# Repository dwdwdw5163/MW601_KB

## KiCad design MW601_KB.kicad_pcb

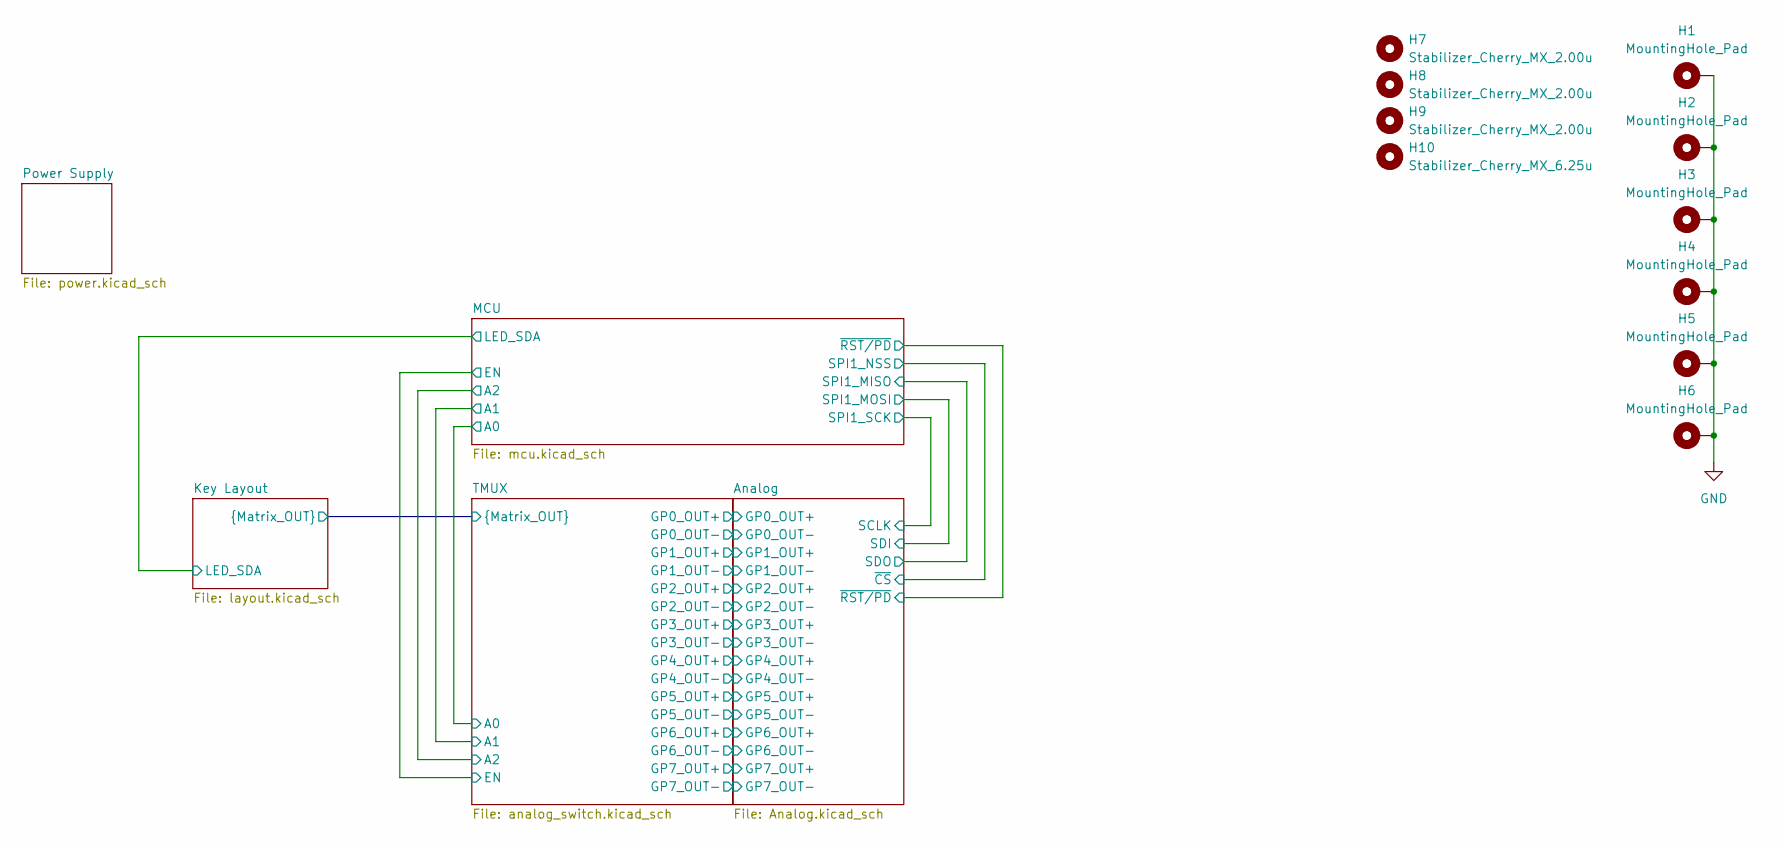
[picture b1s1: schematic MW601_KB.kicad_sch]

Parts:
H1: MountingHole_Pad; PKRHC
H2, H3, H6: MountingHole_Pad; PKRH
H4, H5: MountingHole_Pad; PKRHSL
H7, H8, H9: Stabilizer_Cherry_MX_2.00u
H10: Stabilizer_Cherry_MX_6.25u

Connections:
GND: H1.1, H2.1, H3.1, H4.1, H5.1, H6.1; also elsewhere on the board

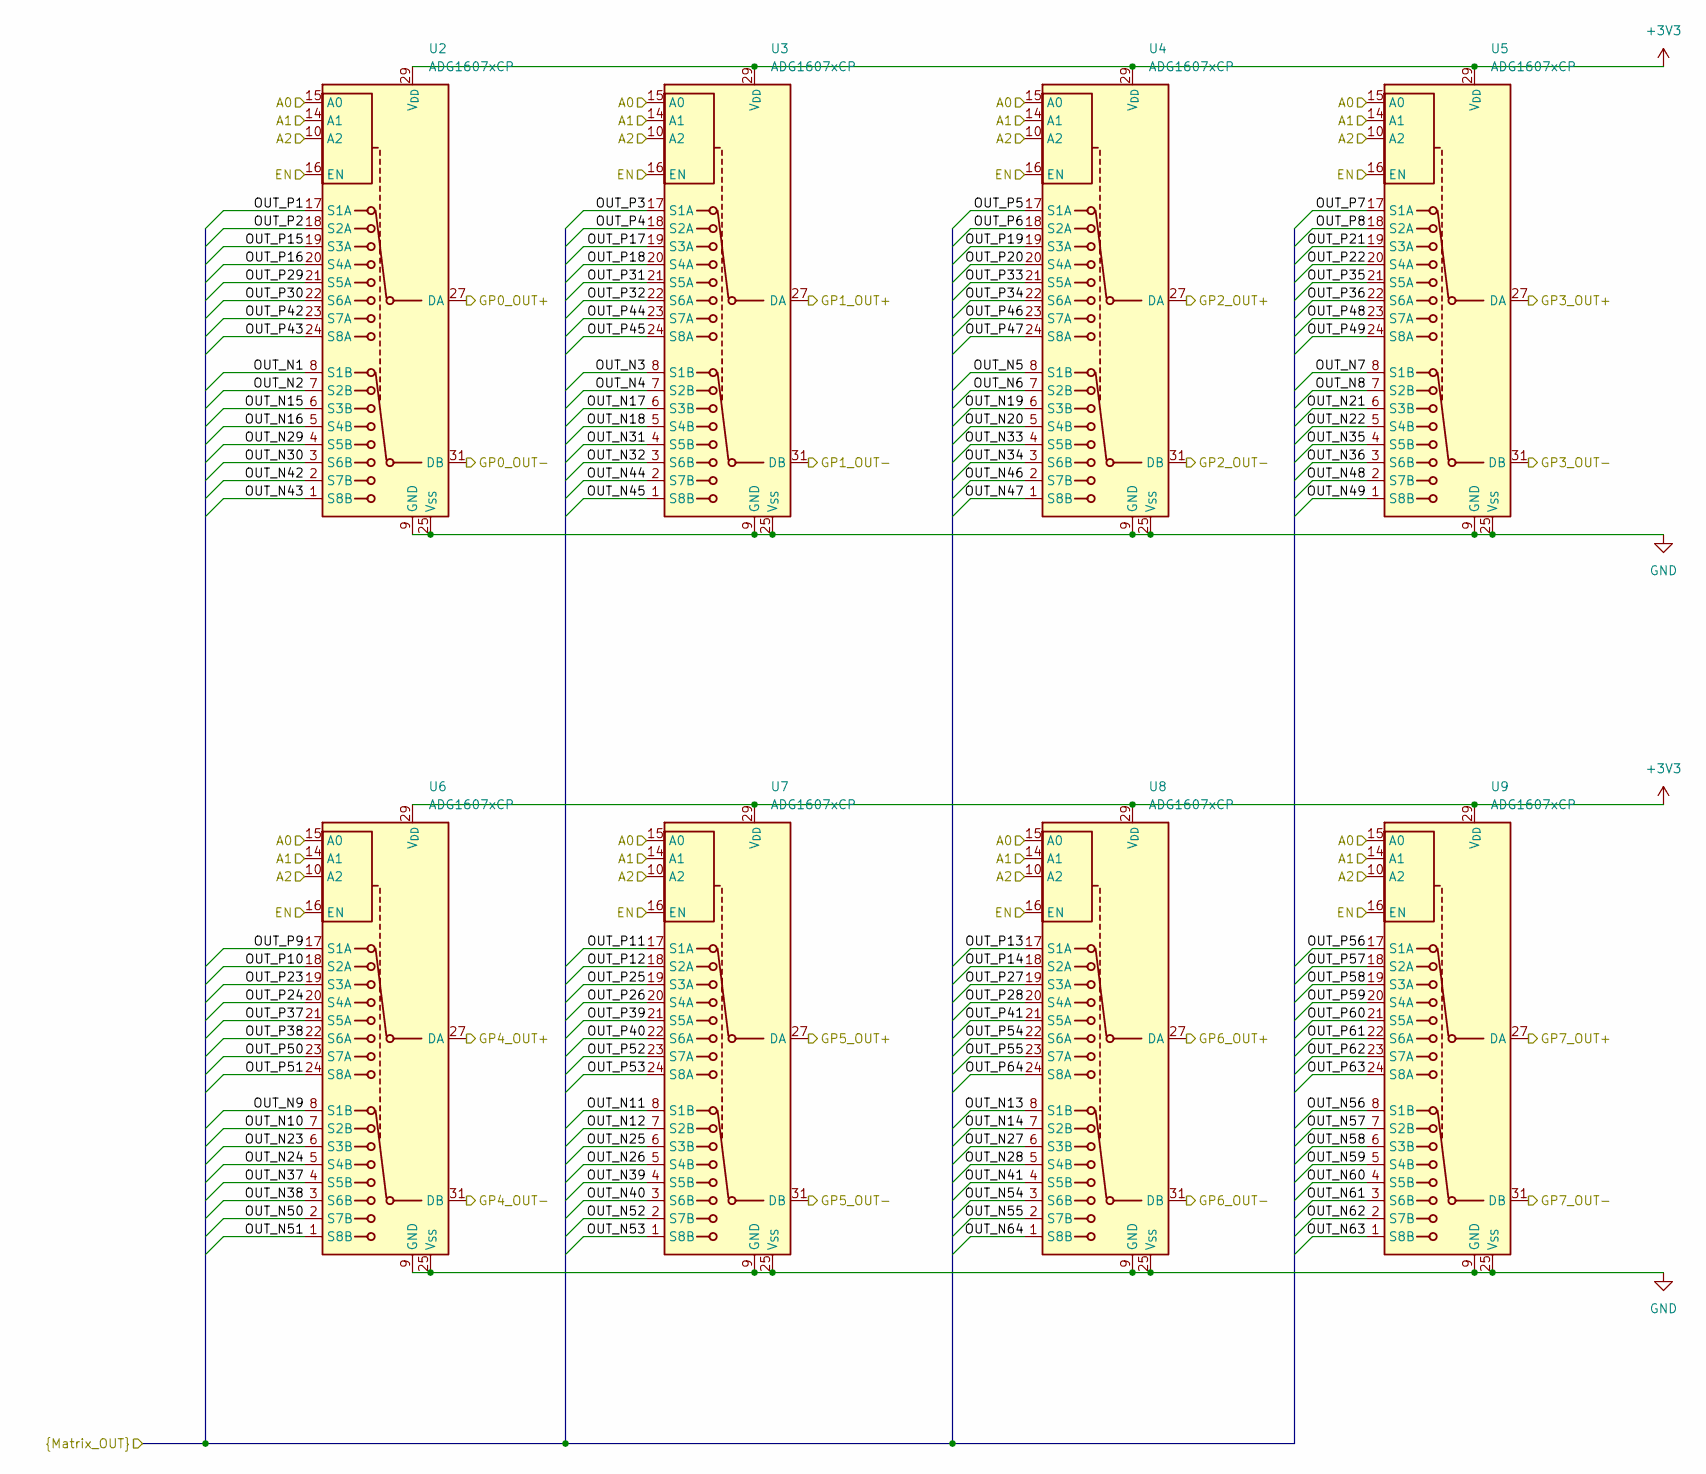
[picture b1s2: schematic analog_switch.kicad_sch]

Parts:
U2, U3, U4, U5, U6, U7, U8, U9: ADG1607xCP; LFCSP-32-1EP_5x5mm_P0.5mm_EP3.1x3.1mm

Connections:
+3V3: U2.29 (V_{DD}), U3.29 (V_{DD}), U4.29 (V_{DD}), U5.29 (V_{DD}), U6.29 (V_{DD}), U7.29 (V_{DD}), U8.29 (V_{DD}), U9.29 (V_{DD}); also elsewhere on the board
/Analog/GP0_OUT+: U2.27 (DA); also elsewhere on the board
/Analog/GP0_OUT-: U2.31 (DB); also elsewhere on the board
/Analog/GP1_OUT+: U3.27 (DA); also elsewhere on the board
/Analog/GP1_OUT-: U3.31 (DB); also elsewhere on the board
/Analog/GP2_OUT+: U4.27 (DA); also elsewhere on the board
/Analog/GP2_OUT-: U4.31 (DB); also elsewhere on the board
/Analog/GP3_OUT+: U5.27 (DA); also elsewhere on the board
/Analog/GP3_OUT-: U5.31 (DB); also elsewhere on the board
/Analog/GP4_OUT+: U6.27 (DA); also elsewhere on the board
/Analog/GP4_OUT-: U6.31 (DB); also elsewhere on the board
/Analog/GP5_OUT+: U7.27 (DA); also elsewhere on the board
/Analog/GP5_OUT-: U7.31 (DB); also elsewhere on the board
/Analog/GP6_OUT+: U8.27 (DA); also elsewhere on the board
/Analog/GP6_OUT-: U8.31 (DB); also elsewhere on the board
/Analog/GP7_OUT+: U9.27 (DA); also elsewhere on the board
/Analog/GP7_OUT-: U9.31 (DB); also elsewhere on the board
/Key Layout/OUT_N1: U2.8 (S1B); also elsewhere on the board
/Key Layout/OUT_N2: U2.7 (S2B); also elsewhere on the board
/Key Layout/OUT_N3: U3.8 (S1B); also elsewhere on the board
/Key Layout/OUT_N4: U3.7 (S2B); also elsewhere on the board
/Key Layout/OUT_N5: U4.8 (S1B); also elsewhere on the board
/Key Layout/OUT_N6: U4.7 (S2B); also elsewhere on the board
/Key Layout/OUT_N7: U5.8 (S1B); also elsewhere on the board
/Key Layout/OUT_N8: U5.7 (S2B); also elsewhere on the board
/Key Layout/OUT_N9: U6.8 (S1B); also elsewhere on the board
/Key Layout/OUT_N10: U6.7 (S2B); also elsewhere on the board
/Key Layout/OUT_N11: U7.8 (S1B); also elsewhere on the board
/Key Layout/OUT_N12: U7.7 (S2B); also elsewhere on the board
/Key Layout/OUT_N13: U8.8 (S1B); also elsewhere on the board
/Key Layout/OUT_N14: U8.7 (S2B); also elsewhere on the board
/Key Layout/OUT_N15: U2.6 (S3B); also elsewhere on the board
/Key Layout/OUT_N16: U2.5 (S4B); also elsewhere on the board
/Key Layout/OUT_N17: U3.6 (S3B); also elsewhere on the board
/Key Layout/OUT_N18: U3.5 (S4B); also elsewhere on the board
/Key Layout/OUT_N19: U4.6 (S3B); also elsewhere on the board
/Key Layout/OUT_N20: U4.5 (S4B); also elsewhere on the board
/Key Layout/OUT_N21: U5.6 (S3B); also elsewhere on the board
/Key Layout/OUT_N22: U5.5 (S4B); also elsewhere on the board
/Key Layout/OUT_N23: U6.6 (S3B); also elsewhere on the board
/Key Layout/OUT_N24: U6.5 (S4B); also elsewhere on the board
/Key Layout/OUT_N25: U7.6 (S3B); also elsewhere on the board
/Key Layout/OUT_N26: U7.5 (S4B); also elsewhere on the board
/Key Layout/OUT_N27: U8.6 (S3B); also elsewhere on the board
/Key Layout/OUT_N28: U8.5 (S4B); also elsewhere on the board
/Key Layout/OUT_N29: U2.4 (S5B); also elsewhere on the board
/Key Layout/OUT_N30: U2.3 (S6B); also elsewhere on the board
/Key Layout/OUT_N31: U3.4 (S5B); also elsewhere on the board
/Key Layout/OUT_N32: U3.3 (S6B); also elsewhere on the board
/Key Layout/OUT_N33: U4.4 (S5B); also elsewhere on the board
/Key Layout/OUT_N34: U4.3 (S6B); also elsewhere on the board
/Key Layout/OUT_N35: U5.4 (S5B); also elsewhere on the board
/Key Layout/OUT_N36: U5.3 (S6B); also elsewhere on the board
/Key Layout/OUT_N37: U6.4 (S5B); also elsewhere on the board
/Key Layout/OUT_N38: U6.3 (S6B); also elsewhere on the board
/Key Layout/OUT_N39: U7.4 (S5B); also elsewhere on the board
/Key Layout/OUT_N40: U7.3 (S6B); also elsewhere on the board
/Key Layout/OUT_N41: U8.4 (S5B); also elsewhere on the board
/Key Layout/OUT_N42: U2.2 (S7B); also elsewhere on the board
/Key Layout/OUT_N43: U2.1 (S8B); also elsewhere on the board
/Key Layout/OUT_N44: U3.2 (S7B); also elsewhere on the board
/Key Layout/OUT_N45: U3.1 (S8B); also elsewhere on the board
/Key Layout/OUT_N46: U4.2 (S7B); also elsewhere on the board
/Key Layout/OUT_N47: U4.1 (S8B); also elsewhere on the board
/Key Layout/OUT_N48: U5.2 (S7B); also elsewhere on the board
/Key Layout/OUT_N49: U5.1 (S8B); also elsewhere on the board
/Key Layout/OUT_N50: U6.2 (S7B); also elsewhere on the board
/Key Layout/OUT_N51: U6.1 (S8B); also elsewhere on the board
/Key Layout/OUT_N52: U7.2 (S7B); also elsewhere on the board
/Key Layout/OUT_N53: U7.1 (S8B); also elsewhere on the board
/Key Layout/OUT_N54: U8.3 (S6B); also elsewhere on the board
/Key Layout/OUT_N55: U8.2 (S7B); also elsewhere on the board
/Key Layout/OUT_N56: U9.8 (S1B); also elsewhere on the board
/Key Layout/OUT_N57: U9.7 (S2B); also elsewhere on the board
/Key Layout/OUT_N58: U9.6 (S3B); also elsewhere on the board
/Key Layout/OUT_N59: U9.5 (S4B); also elsewhere on the board
/Key Layout/OUT_N60: U9.4 (S5B); also elsewhere on the board
/Key Layout/OUT_N61: U9.3 (S6B); also elsewhere on the board
/Key Layout/OUT_N62: U9.2 (S7B); also elsewhere on the board
/Key Layout/OUT_N63: U9.1 (S8B); also elsewhere on the board
/Key Layout/OUT_N64: U8.1 (S8B); also elsewhere on the board
/Key Layout/OUT_P1: U2.17 (S1A); also elsewhere on the board
/Key Layout/OUT_P2: U2.18 (S2A); also elsewhere on the board
/Key Layout/OUT_P3: U3.17 (S1A); also elsewhere on the board
/Key Layout/OUT_P4: U3.18 (S2A); also elsewhere on the board
/Key Layout/OUT_P5: U4.17 (S1A); also elsewhere on the board
/Key Layout/OUT_P6: U4.18 (S2A); also elsewhere on the board
/Key Layout/OUT_P7: U5.17 (S1A); also elsewhere on the board
/Key Layout/OUT_P8: U5.18 (S2A); also elsewhere on the board
/Key Layout/OUT_P9: U6.17 (S1A); also elsewhere on the board
/Key Layout/OUT_P10: U6.18 (S2A); also elsewhere on the board
/Key Layout/OUT_P11: U7.17 (S1A); also elsewhere on the board
/Key Layout/OUT_P12: U7.18 (S2A); also elsewhere on the board
/Key Layout/OUT_P13: U8.17 (S1A); also elsewhere on the board
/Key Layout/OUT_P14: U8.18 (S2A); also elsewhere on the board
/Key Layout/OUT_P15: U2.19 (S3A); also elsewhere on the board
/Key Layout/OUT_P16: U2.20 (S4A); also elsewhere on the board
/Key Layout/OUT_P17: U3.19 (S3A); also elsewhere on the board
/Key Layout/OUT_P18: U3.20 (S4A); also elsewhere on the board
/Key Layout/OUT_P19: U4.19 (S3A); also elsewhere on the board
/Key Layout/OUT_P20: U4.20 (S4A); also elsewhere on the board
/Key Layout/OUT_P21: U5.19 (S3A); also elsewhere on the board
/Key Layout/OUT_P22: U5.20 (S4A); also elsewhere on the board
/Key Layout/OUT_P23: U6.19 (S3A); also elsewhere on the board
/Key Layout/OUT_P24: U6.20 (S4A); also elsewhere on the board
/Key Layout/OUT_P25: U7.19 (S3A); also elsewhere on the board
/Key Layout/OUT_P26: U7.20 (S4A); also elsewhere on the board
/Key Layout/OUT_P27: U8.19 (S3A); also elsewhere on the board
/Key Layout/OUT_P28: U8.20 (S4A); also elsewhere on the board
/Key Layout/OUT_P29: U2.21 (S5A); also elsewhere on the board
/Key Layout/OUT_P30: U2.22 (S6A); also elsewhere on the board
/Key Layout/OUT_P31: U3.21 (S5A); also elsewhere on the board
/Key Layout/OUT_P32: U3.22 (S6A); also elsewhere on the board
/Key Layout/OUT_P33: U4.21 (S5A); also elsewhere on the board
/Key Layout/OUT_P34: U4.22 (S6A); also elsewhere on the board
/Key Layout/OUT_P35: U5.21 (S5A); also elsewhere on the board
/Key Layout/OUT_P36: U5.22 (S6A); also elsewhere on the board
/Key Layout/OUT_P37: U6.21 (S5A); also elsewhere on the board
/Key Layout/OUT_P38: U6.22 (S6A); also elsewhere on the board
/Key Layout/OUT_P39: U7.21 (S5A); also elsewhere on the board
/Key Layout/OUT_P40: U7.22 (S6A); also elsewhere on the board
/Key Layout/OUT_P41: U8.21 (S5A); also elsewhere on the board
/Key Layout/OUT_P42: U2.23 (S7A); also elsewhere on the board
/Key Layout/OUT_P43: U2.24 (S8A); also elsewhere on the board
/Key Layout/OUT_P44: U3.23 (S7A); also elsewhere on the board
/Key Layout/OUT_P45: U3.24 (S8A); also elsewhere on the board
/Key Layout/OUT_P46: U4.23 (S7A); also elsewhere on the board
/Key Layout/OUT_P47: U4.24 (S8A); also elsewhere on the board
/Key Layout/OUT_P48: U5.23 (S7A); also elsewhere on the board
/Key Layout/OUT_P49: U5.24 (S8A); also elsewhere on the board
/Key Layout/OUT_P50: U6.23 (S7A); also elsewhere on the board
/Key Layout/OUT_P51: U6.24 (S8A); also elsewhere on the board
/Key Layout/OUT_P52: U7.23 (S7A); also elsewhere on the board
/Key Layout/OUT_P53: U7.24 (S8A); also elsewhere on the board
/Key Layout/OUT_P54: U8.22 (S6A); also elsewhere on the board
/Key Layout/OUT_P55: U8.23 (S7A); also elsewhere on the board
/Key Layout/OUT_P56: U9.17 (S1A); also elsewhere on the board
/Key Layout/OUT_P57: U9.18 (S2A); also elsewhere on the board
/Key Layout/OUT_P58: U9.19 (S3A); also elsewhere on the board
/Key Layout/OUT_P59: U9.20 (S4A); also elsewhere on the board
/Key Layout/OUT_P60: U9.21 (S5A); also elsewhere on the board
/Key Layout/OUT_P61: U9.22 (S6A); also elsewhere on the board
/Key Layout/OUT_P62: U9.23 (S7A); also elsewhere on the board
/Key Layout/OUT_P63: U9.24 (S8A); also elsewhere on the board
/Key Layout/OUT_P64: U8.24 (S8A); also elsewhere on the board
/MCU/A0: U2.15 (A0), U3.15 (A0), U4.15 (A0), U5.15 (A0), U6.15 (A0), U7.15 (A0), U8.15 (A0), U9.15 (A0); also elsewhere on the board
/MCU/A1: U2.14 (A1), U3.14 (A1), U4.14 (A1), U5.14 (A1), U6.14 (A1), U7.14 (A1), U8.14 (A1), U9.14 (A1); also elsewhere on the board
/MCU/A2: U2.10 (A2), U3.10 (A2), U4.10 (A2), U5.10 (A2), U6.10 (A2), U7.10 (A2), U8.10 (A2), U9.10 (A2); also elsewhere on the board
/MCU/EN: U2.16 (EN), U3.16 (EN), U4.16 (EN), U5.16 (EN), U6.16 (EN), U7.16 (EN), U8.16 (EN), U9.16 (EN); also elsewhere on the board
GND: U2.9 (GND), U2.25 (V_{SS}), U2.33 (V_{SS}), U3.9 (GND), U3.25 (V_{SS}), U3.33 (V_{SS}), U4.9 (GND), U4.25 (V_{SS}), U4.33 (V_{SS}), U5.9 (GND), U5.25 (V_{SS}), U5.33 (V_{SS}), U6.9 (GND), U6.25 (V_{SS}), U6.33 (V_{SS}), U7.9 (GND), U7.25 (V_{SS}), U7.33 (V_{SS}), U8.9 (GND), U8.25 (V_{SS}), U8.33 (V_{SS}), U9.9 (GND), U9.25 (V_{SS}), U9.33 (V_{SS}); also elsewhere on the board

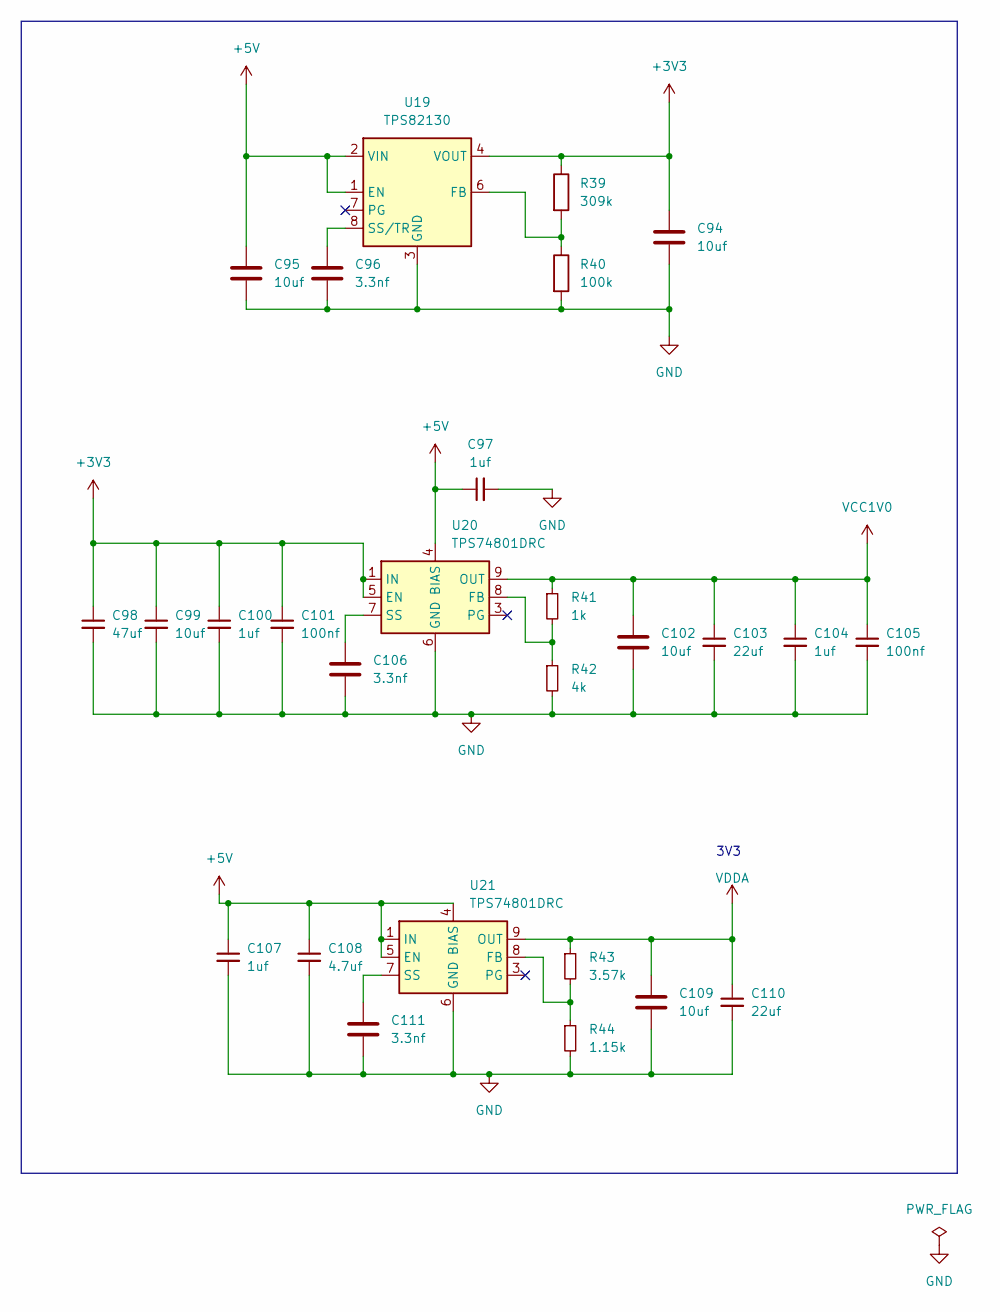
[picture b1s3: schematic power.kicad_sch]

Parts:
C94, C95, C99, C102, C109: 10uf; C_0805_2012Metric
C96, C106, C111: 3.3nf; C_0603_1608Metric
C97, C100, C104, C107: 1uf; C_0603_1608Metric
C98: 47uf; C_0805_2012Metric
C101, C105: 100nf; C_0603_1608Metric
C103, C110: 22uf; C_0805_2012Metric
C108: 4.7uf; C_0603_1608Metric
R39: 309k; R_0603_1608Metric
R40: 100k; R_0603_1608Metric
R41: 1k; R_0603_1608Metric
R42: 4k; R_0603_1608Metric
R43: 3.57k; R_0603_1608Metric
R44: 1.15k; R_0603_1608Metric
U19: TPS82130; Texas_SIL0008D_MicroSiP-8-1EP_2.8x3mm_P0.65mm_EP1.1x1.9mm_T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
U20, U21: TPS74801DRC; VSON-10-1EP_3x3mm_P0.5mm_EP1.65x2.4mm_ThermalVias

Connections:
+3V3: C94.1, C98.1, C99.1, C100.1, C101.1, R39.1, U19.4 (VOUT), U19.5 (VOUT), U20.1 (IN), U20.2 (IN), U20.5 (EN); also elsewhere on the board
+5V: C95.1, C97.1, C107.1, C108.1, U19.1 (EN), U19.2 (VIN), U20.4 (BIAS), U21.1 (IN), U21.2 (IN), U21.4 (BIAS), U21.5 (EN); also elsewhere on the board
GND: C94.2, C95.2, C96.2, C97.2, C98.2, C99.2, C100.2, C101.2, C102.2, C103.2, C104.2, C105.2, C106.2, C107.2, C108.2, C109.2, C110.2, C111.2, R40.2, R42.2, R44.2, U19.3 (GND), U19.9 (GND), U20.6 (GND), U20.11 (GND), U21.6 (GND), U21.11 (GND); also elsewhere on the board
unnamed: R39.2, R40.1, U19.6 (FB)
unnamed: C96.1, U19.8 (SS/TR)
unnamed: R41.2, R42.1, U20.8 (FB)
unnamed: C106.1, U20.7 (SS)
unnamed: R43.2, R44.1, U21.8 (FB)
unnamed: C111.1, U21.7 (SS)
VCC1V0: C102.1, C103.1, C104.1, C105.1, R41.1, U20.9 (OUT), U20.10 (OUT); also elsewhere on the board
VDDA: C109.1, C110.1, R43.1, U21.9 (OUT), U21.10 (OUT); also elsewhere on the board

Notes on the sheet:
3V3

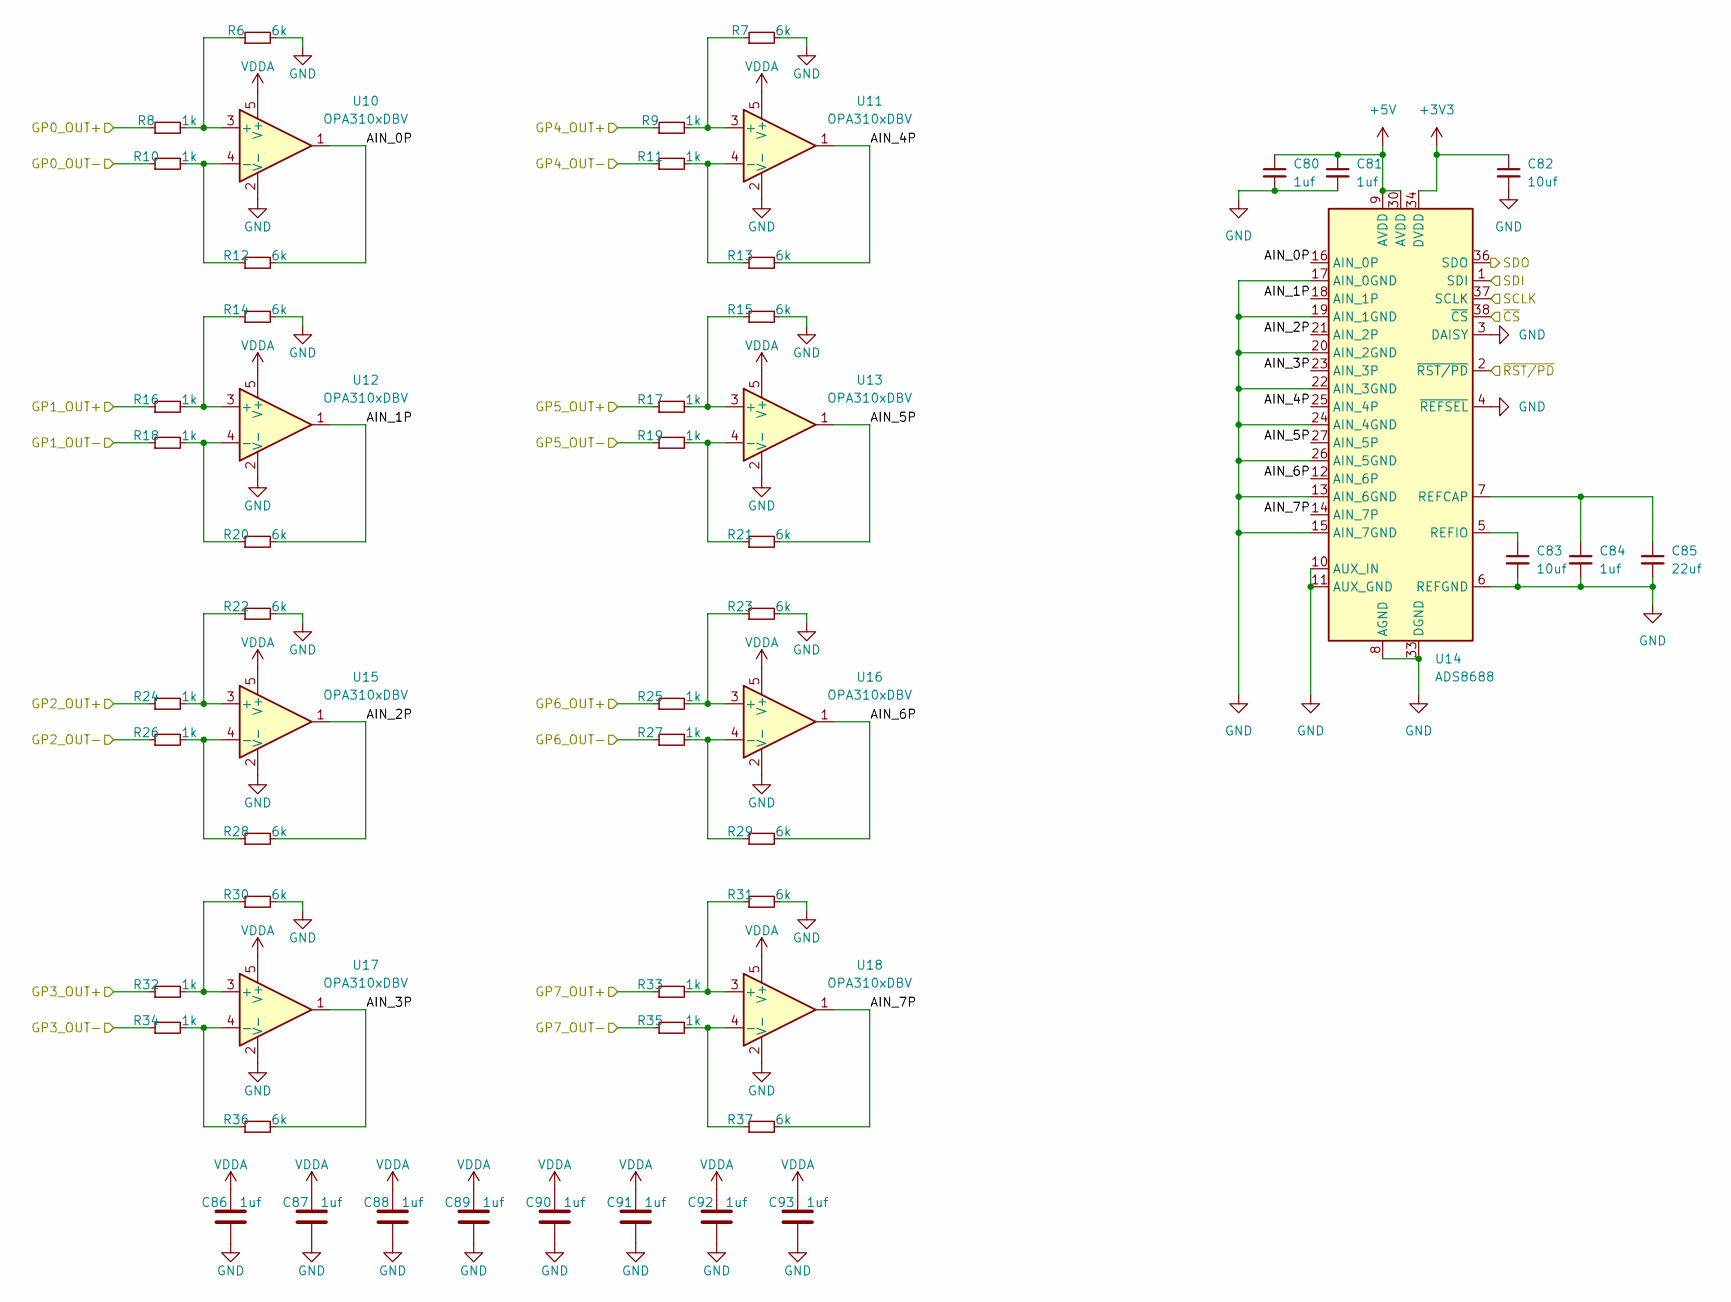
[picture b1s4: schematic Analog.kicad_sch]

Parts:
C80, C81, C84, C86, C87, C88, C89, C90, C91, C92, C93: 1uf; C_0603_1608Metric
C82, C83: 10uf; C_0805_2012Metric
C85: 22uf; C_0805_2012Metric
R6, R7, R12, R13, R14, R15, R20, R21, R22, R23, R28, R29, R30, R31, R36, R37: 6k; R_0603_1608Metric
R8, R9, R10, R11, R16, R17, R18, R19, R24, R25, R26, R27, R32, R33, R34, R35: 1k; R_0603_1608Metric
U10, U11, U12, U13, U15, U16, U17, U18: OPA310xDBV; SOT-23-5
U14: ADS8688; TSSOP-38_4.4x9.7mm_P0.5mm

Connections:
+3V3: C82.1, U14.34 (DVDD); also elsewhere on the board
+5V: C80.1, C81.1, U14.9 (AVDD), U14.30 (AVDD); also elsewhere on the board
/Analog/AIN_0P: R12.2, U10.1, U14.16 (AIN_0P)
/Analog/AIN_1P: R20.2, U12.1, U14.18 (AIN_1P)
/Analog/AIN_2P: R28.2, U14.21 (AIN_2P), U15.1
/Analog/AIN_3P: R36.2, U14.23 (AIN_3P), U17.1
/Analog/AIN_4P: R13.2, U11.1, U14.25 (AIN_4P)
/Analog/AIN_5P: R21.2, U13.1, U14.27 (AIN_5P)
/Analog/AIN_6P: R29.2, U14.12 (AIN_6P), U16.1
/Analog/AIN_7P: R37.2, U14.14 (AIN_7P), U18.1
/Analog/GP0_OUT+: R8.1; also elsewhere on the board
/Analog/GP0_OUT-: R10.1; also elsewhere on the board
/Analog/GP1_OUT+: R16.1; also elsewhere on the board
/Analog/GP1_OUT-: R18.1; also elsewhere on the board
/Analog/GP2_OUT+: R24.1; also elsewhere on the board
/Analog/GP2_OUT-: R26.1; also elsewhere on the board
/Analog/GP3_OUT+: R32.1; also elsewhere on the board
/Analog/GP3_OUT-: R34.1; also elsewhere on the board
/Analog/GP4_OUT+: R9.1; also elsewhere on the board
/Analog/GP4_OUT-: R11.1; also elsewhere on the board
/Analog/GP5_OUT+: R17.1; also elsewhere on the board
/Analog/GP5_OUT-: R19.1; also elsewhere on the board
/Analog/GP6_OUT+: R25.1; also elsewhere on the board
/Analog/GP6_OUT-: R27.1; also elsewhere on the board
/Analog/GP7_OUT+: R33.1; also elsewhere on the board
/Analog/GP7_OUT-: R35.1; also elsewhere on the board
/Analog/SCLK: U14.37 (SCLK); also elsewhere on the board
/Analog/SDI: U14.1 (SDI); also elsewhere on the board
/Analog/SDO: U14.36 (SDO); also elsewhere on the board
/Analog/~CS: U14.38 (~CS); also elsewhere on the board
/Analog/~RST/PD: U14.2 (~RST/PD); also elsewhere on the board
GND: C80.2, C81.2, C82.2, C83.2, C84.2, C85.2, C86.1, C87.1, C88.1, C89.1, C90.1, C91.1, C92.1, C93.1, R6.2, R7.2, R14.2, R15.2, R22.2, R23.2, R30.2, R31.2, U10.2 (V-), U11.2 (V-), U12.2 (V-), U13.2 (V-), U14.3 (DAISY), U14.4 (~REFSEL), U14.6 (REFGND), U14.8 (AGND), U14.10 (AUX_IN), U14.11 (AUX_GND), U14.13 (AIN_6GND), U14.15 (AIN_7GND), U14.17 (AIN_0GND), U14.19 (AIN_1GND), U14.20 (AIN_2GND), U14.22 (AIN_3GND), U14.24 (AIN_4GND), U14.26 (AIN_5GND), U14.28 (AGND), U14.29 (AGND), U14.31 (AGND), U14.32 (AGND), U14.33 (DGND), U15.2 (V-), U16.2 (V-), U17.2 (V-), U18.2 (V-); also elsewhere on the board
unnamed: R6.1, R8.2, U10.3 (+)
unnamed: R10.2, R12.1, U10.4 (-)
unnamed: R7.1, R9.2, U11.3 (+)
unnamed: R11.2, R13.1, U11.4 (-)
unnamed: R14.1, R16.2, U12.3 (+)
unnamed: R18.2, R20.1, U12.4 (-)
unnamed: R15.1, R17.2, U13.3 (+)
unnamed: R19.2, R21.1, U13.4 (-)
unnamed: C84.1, C85.1, U14.7 (REFCAP)
unnamed: C83.1, U14.5 (REFIO)
unnamed: R22.1, R24.2, U15.3 (+)
unnamed: R26.2, R28.1, U15.4 (-)
unnamed: R23.1, R25.2, U16.3 (+)
unnamed: R27.2, R29.1, U16.4 (-)
unnamed: R30.1, R32.2, U17.3 (+)
unnamed: R34.2, R36.1, U17.4 (-)
unnamed: R31.1, R33.2, U18.3 (+)
unnamed: R35.2, R37.1, U18.4 (-)
VDDA: C86.2, C87.2, C88.2, C89.2, C90.2, C91.2, C92.2, C93.2, U10.5 (V+), U11.5 (V+), U12.5 (V+), U13.5 (V+), U15.5 (V+), U16.5 (V+), U17.5 (V+), U18.5 (V+); also elsewhere on the board

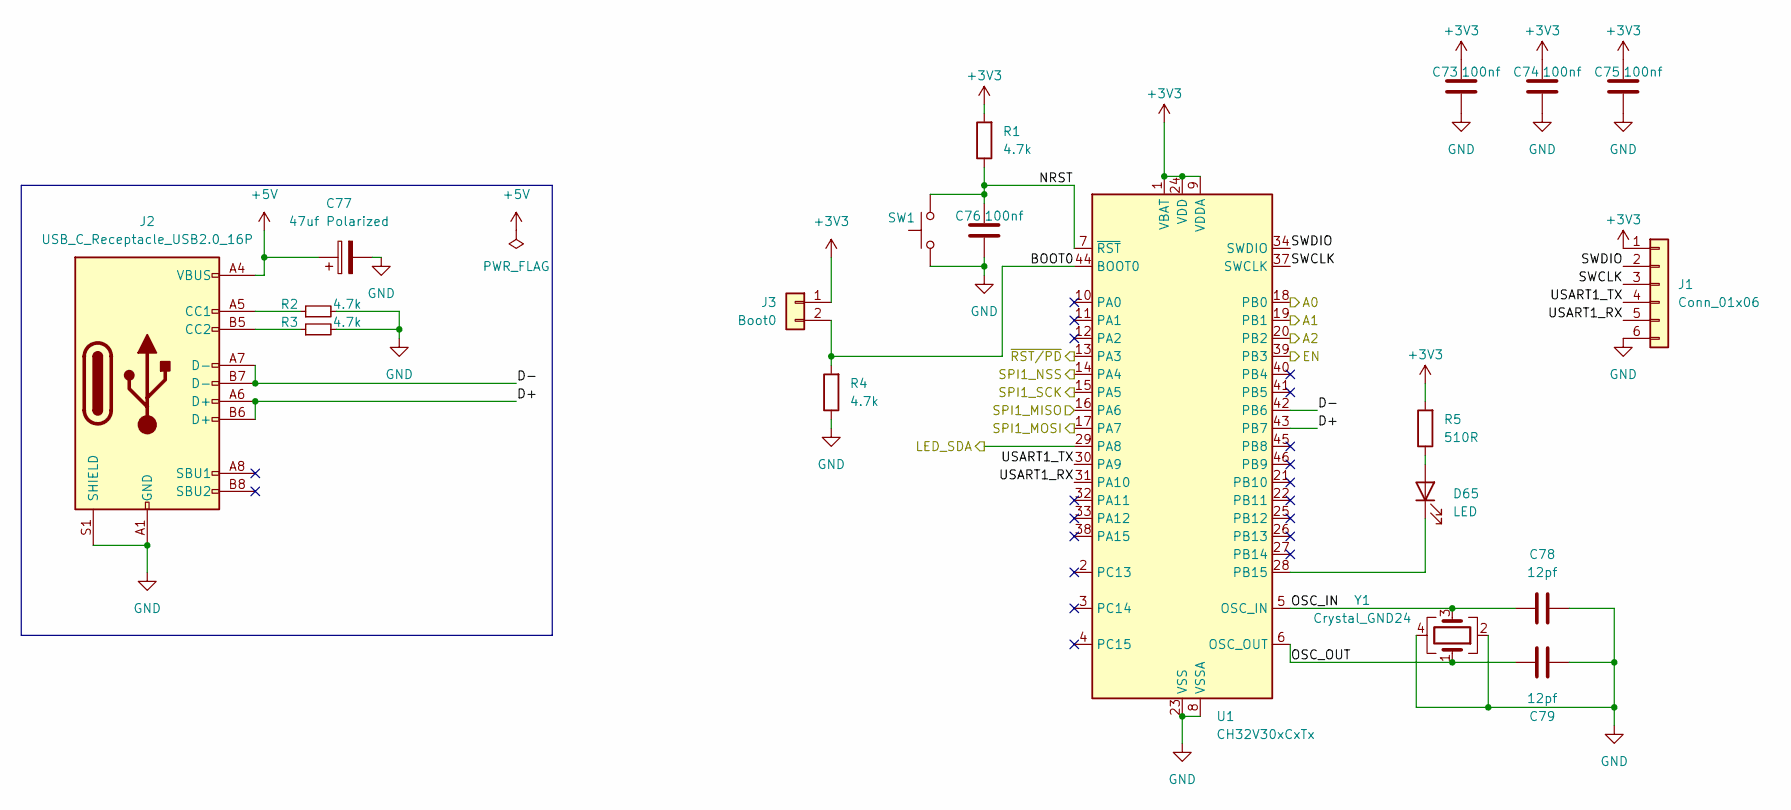
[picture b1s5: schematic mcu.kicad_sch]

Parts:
C73, C74, C75, C76: 100nf; C_0603_1608Metric
C77: 47uf Polarized; CP_EIA-3528-21_Kemet-B
C78, C79: 12pf; C_0603_1608Metric
D65: LED; LED_0603_1608Metric
J1: Conn_01x06; PinHeader_1x06_P2.54mm_Vertical
J2: USB_C_Receptacle_USB2.0_16P; USB_C_Receptacle_XKB_U262-16XN-4BVC11
J3: Boot0; PinHeader_1x02_P2.54mm_Vertical
R1, R2, R3, R4: 4.7k; R_0603_1608Metric
R5: 510R; R_0603_1608Metric
SW1: SW_Push; SW_Push_1P1T_XKB_TS-1187A
U1: CH32V30xCxTx; LQFP-48_7x7mm_P0.5mm
Y1: Crystal_GND24; Crystal_SMD_3225-4Pin_3.2x2.5mm

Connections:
+3V3: C73.2, C74.2, C75.2, J1.1, J3.1, R1.2, R5.2, U1.1 (VBAT), U1.9 (VDDA), U1.24 (VDD), U1.36 (VDD), U1.48 (VDD); also elsewhere on the board
+5V: C77.1, J2.A4 (VBUS), J2.A9 (VBUS), J2.B4 (VBUS), J2.B9 (VBUS); also elsewhere on the board
/Analog/SCLK: U1.15 (PA5); also elsewhere on the board
/Analog/SDI: U1.17 (PA7); also elsewhere on the board
/Analog/SDO: U1.16 (PA6); also elsewhere on the board
/Analog/~CS: U1.14 (PA4); also elsewhere on the board
/Analog/~RST/PD: U1.13 (PA3); also elsewhere on the board
/Key Layout/LED_SDA: U1.29 (PA8); also elsewhere on the board
/MCU/A0: U1.18 (PB0); also elsewhere on the board
/MCU/A1: U1.19 (PB1); also elsewhere on the board
/MCU/A2: U1.20 (PB2); also elsewhere on the board
/MCU/BOOT0: J3.2, R4.2, U1.44 (BOOT0)
/MCU/D+: J2.A6 (D+), J2.B6 (D+), U1.43 (PB7)
/MCU/D-: J2.A7 (D-), J2.B7 (D-), U1.42 (PB6)
/MCU/EN: U1.39 (PB3); also elsewhere on the board
/MCU/NRST: C76.2, R1.1, SW1.2, U1.7 (~RST)
/MCU/OSC_IN: C78.2, U1.5 (OSC_IN), Y1.3
/MCU/OSC_OUT: C79.2, U1.6 (OSC_OUT), Y1.1
/MCU/SWCLK: J1.3, U1.37 (SWCLK)
/MCU/SWDIO: J1.2, U1.34 (SWDIO)
/MCU/USART1_RX: J1.5, U1.31 (PA10)
/MCU/USART1_TX: J1.4, U1.30 (PA9)
GND: C73.1, C74.1, C75.1, C76.1, C77.2, C78.1, C79.1, J1.6, J2.A1 (GND), J2.A12 (GND), J2.B1 (GND), J2.B12 (GND), J2.S1 (SHIELD), R2.2, R3.2, R4.1, SW1.1, U1.8 (VSSA), U1.23 (VSS), U1.35 (VSS), U1.47 (VSS), Y1.2, Y1.4; also elsewhere on the board
unnamed: D65.2 (A), R5.1
unnamed: D65.1 (K), U1.28 (PB15)
unnamed: J2.A5 (CC1), R2.1
unnamed: J2.B5 (CC2), R3.1
